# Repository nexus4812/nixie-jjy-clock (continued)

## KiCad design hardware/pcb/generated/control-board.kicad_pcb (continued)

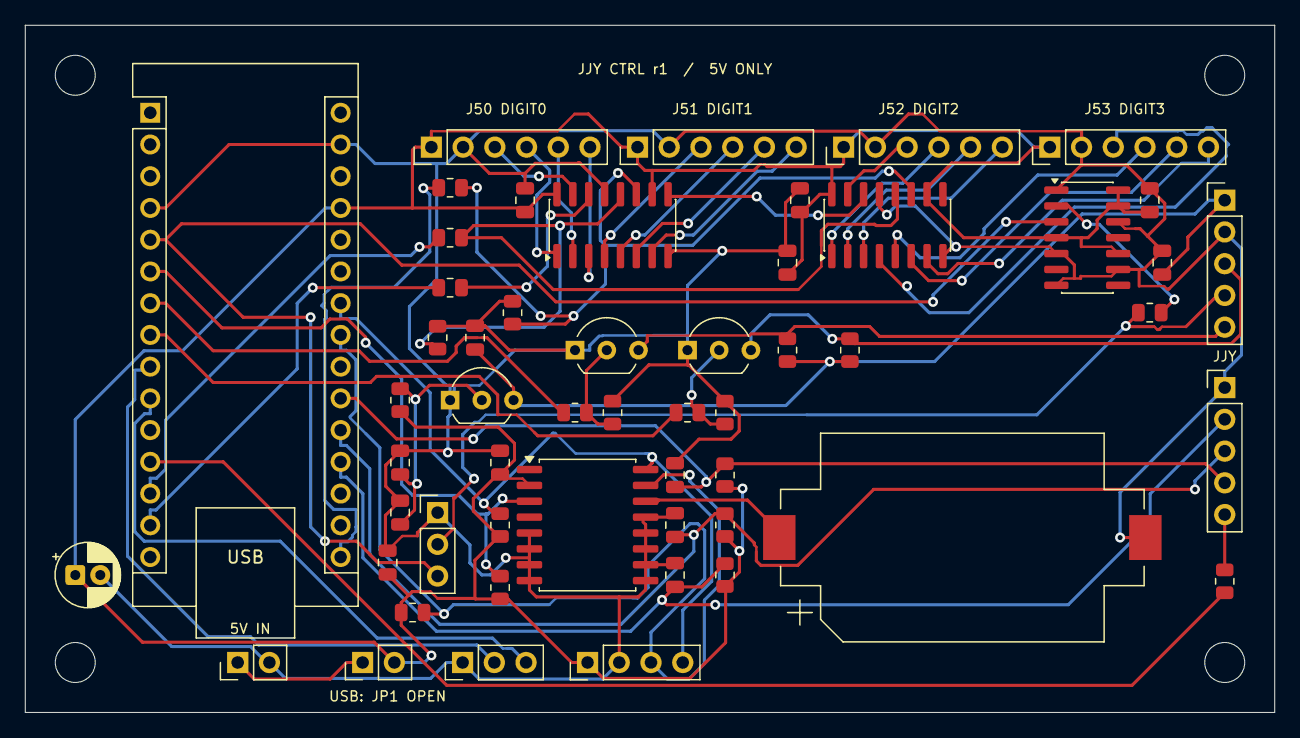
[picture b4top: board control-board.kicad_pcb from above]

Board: 2 copper layers, 100.0 x 55.0 mm, 58 parts (0 on the bottom side), 48 nets.

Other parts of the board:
H1, H2, H3, H4: M3_NPTH_DRAFT; MountingHole_3.2mm_M3
